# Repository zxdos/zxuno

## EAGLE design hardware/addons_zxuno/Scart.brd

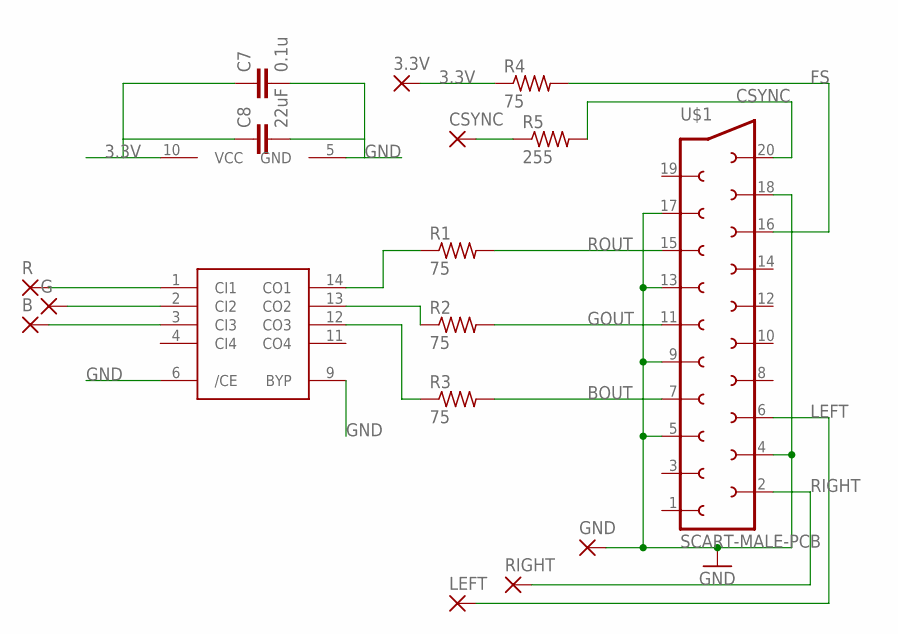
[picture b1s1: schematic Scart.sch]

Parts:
3.3V: WIREPADSMD1,27-254; SMD1,27-2,54
B: WIREPADSMD1,27-254; SMD1,27-2,54
C7: 0.1u; C0805K
C8: 22uF; C0805K
CSYNC: WIREPADSMD1,27-254; SMD1,27-2,54
G: WIREPADSMD1,27-254; SMD1,27-2,54
GND: WIREPADSMD1,27-254; SMD1,27-2,54
LEFT: WIREPADSMD1,27-254; SMD1,27-2,54
R: WIREPADSMD1,27-254; SMD1,27-2,54
R1, R2, R3, R4: 75; R0805
R5: 255; R0805
RIGHT: WIREPADSMD1,27-254; SMD1,27-2,54
U$1: SCART-MALE-PCB; SCART-PCB
U$2: THS7374

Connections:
3.3V: 3.3V.1, C7.1, C8.1, R4.1, U$2.10 (VCC)
BOUT: R3.2, U$1.7
CSYNC: R5.2, U$1.20
FS: R4.2, U$1.16
GND: C7.2, C8.2, GND.1, U$1.4, U$1.5, U$1.9, U$1.13, U$1.17, U$1.18, U$2.5 (GND), U$2.6 (/CE), U$2.9 (BYP)
GOUT: R2.2, U$1.11
LEFT: LEFT.1, U$1.6
unnamed: R.1, U$2.1 (CI1)
unnamed: R1.1, U$2.14 (CO1)
unnamed: R2.1, U$2.13 (CO2)
unnamed: R3.1, U$2.12 (CO3)
unnamed: G.1, U$2.2 (CI2)
unnamed: B.1, U$2.3 (CI3)
unnamed: CSYNC.1, R5.1
RIGHT: RIGHT.1, U$1.2
ROUT: R1.2, U$1.15

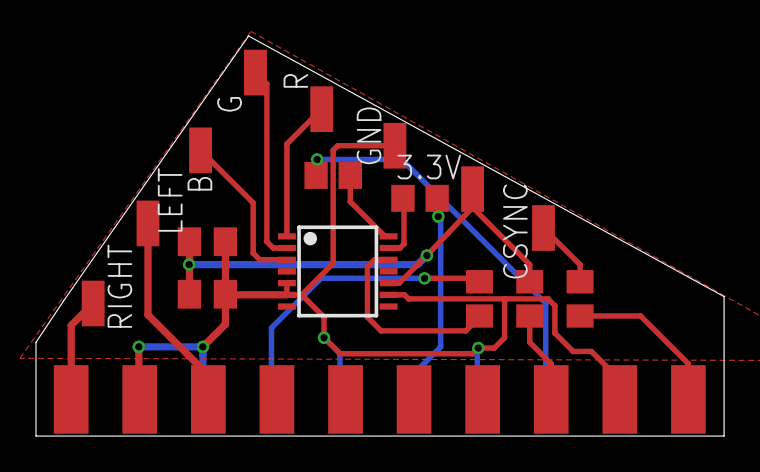
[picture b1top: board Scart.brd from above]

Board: 2 copper layers, 38.2 x 22.2 mm, 17 parts (1 on the bottom side), 16 nets.

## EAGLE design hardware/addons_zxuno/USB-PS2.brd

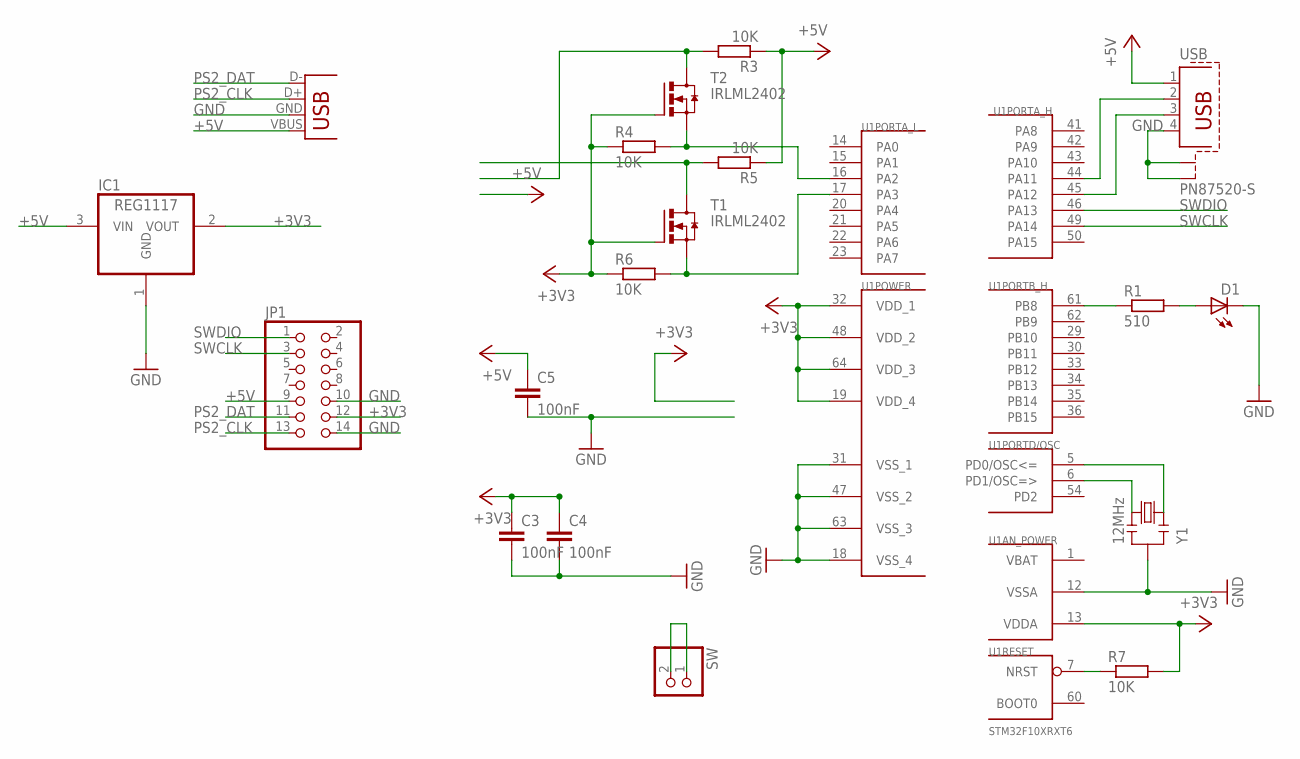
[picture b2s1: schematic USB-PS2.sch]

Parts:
C3, C4, C5: 100nF; C0805
D1: LEDSML0805; SML0805
IC1: REG1117; SOT223
JP1: PINHD-2X7; 2X07
R1: 510; R0805
R3, R4, R5, R6, R7: 10K; R0805
SW: PINHD-1X2; 1X02
T1, T2: IRLML2402; MICRO3
U1: STM32F10XRXT6; TQFP64
USB: PN87520-S
X1: USB-A-H
Y1: 12MHz; RESONATOR

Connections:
+3V3: C3.1, C4.1, IC1.2 (VOUT), JP1.12, R4.1, R6.1, R7.2, T1.1 (G), T2.1 (G), U1.13 (VDDA), U1.19 (VDD_4), U1.32 (VDD_1), U1.48 (VDD_2), U1.64 (VDD_3)
+5V: C5.1, IC1.3 (VIN), JP1.9, R3.1, R5.1, USB.1, X1.VBUS (GND)
GND: C3.2, C4.2, C5.2, D1.C, IC1.1 (GND), JP1.10, JP1.14, U1.12 (VSSA), U1.18 (VSS_4), U1.31 (VSS_1), U1.47 (VSS_2), U1.63 (VSS_3), USB.4, USB.S1, USB.S2, X1.GND (VBUS), Y1.2
unnamed: U1.44 (PA11), USB.2
unnamed: U1.45 (PA12), USB.3
unnamed: R1.1, U1.61 (PB8)
unnamed: U1.5 (PD0/OSC<=), Y1.1
unnamed: D1.A, R1.2
unnamed: U1.6 (PD1/OSC=>), Y1.3
unnamed: R7.1, U1.7 (NRST)
unnamed: SW.1, SW.2
unnamed: R6.2, T1.2 (S), U1.17 (PA3)
unnamed: R4.2, T2.2 (S), U1.16 (PA2)
PS2_CLK: JP1.13, R5.2, T1.3 (D), X1.D+ (D-)
PS2_DAT: JP1.11, R3.2, T2.3 (D), X1.D- (D+)
SWCLK: JP1.3, U1.49 (PA14)
SWDIO: JP1.1, U1.46 (PA13)
VBAT: U1.1 (VBAT)

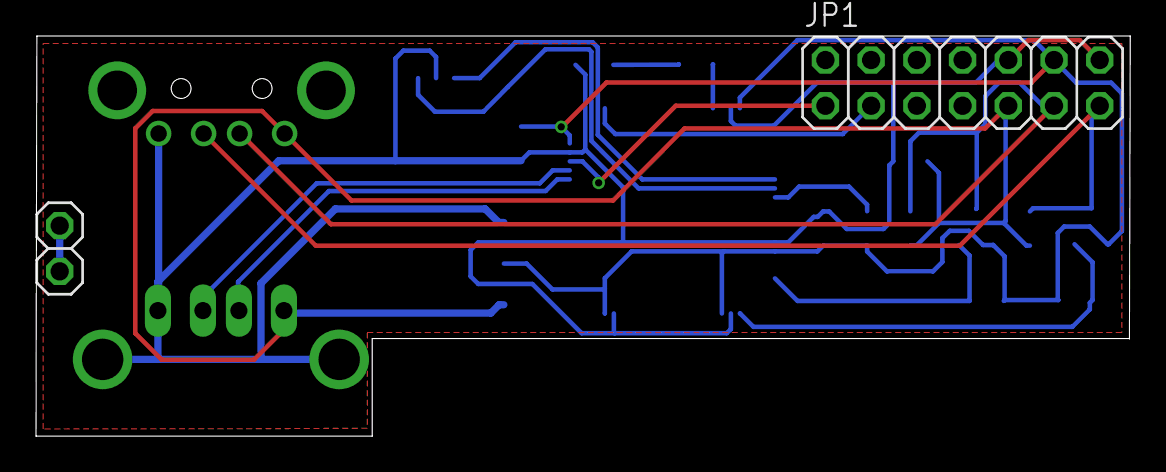
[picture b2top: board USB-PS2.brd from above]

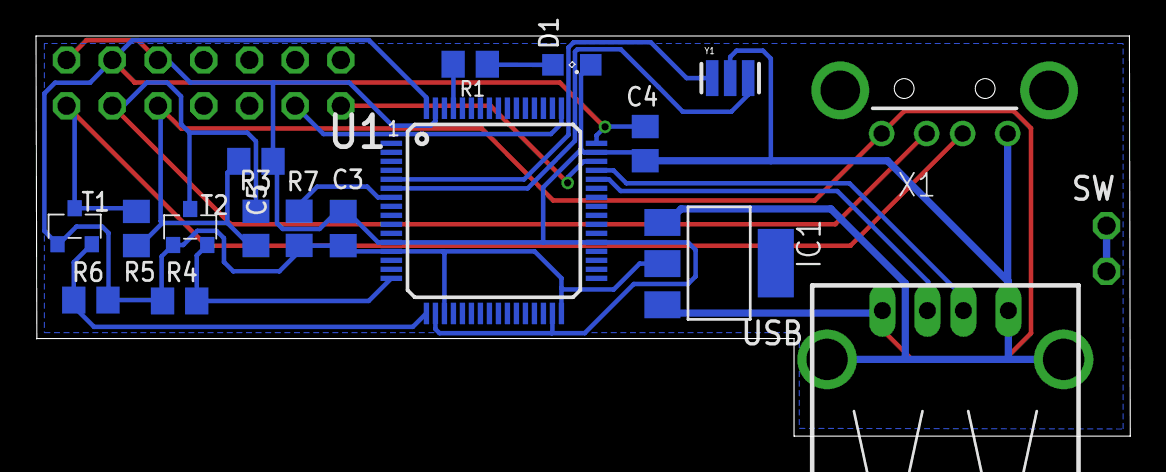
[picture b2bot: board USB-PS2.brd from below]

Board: 2 copper layers, 60.8 x 22.2 mm, 19 parts (17 on the bottom side), 17 nets.

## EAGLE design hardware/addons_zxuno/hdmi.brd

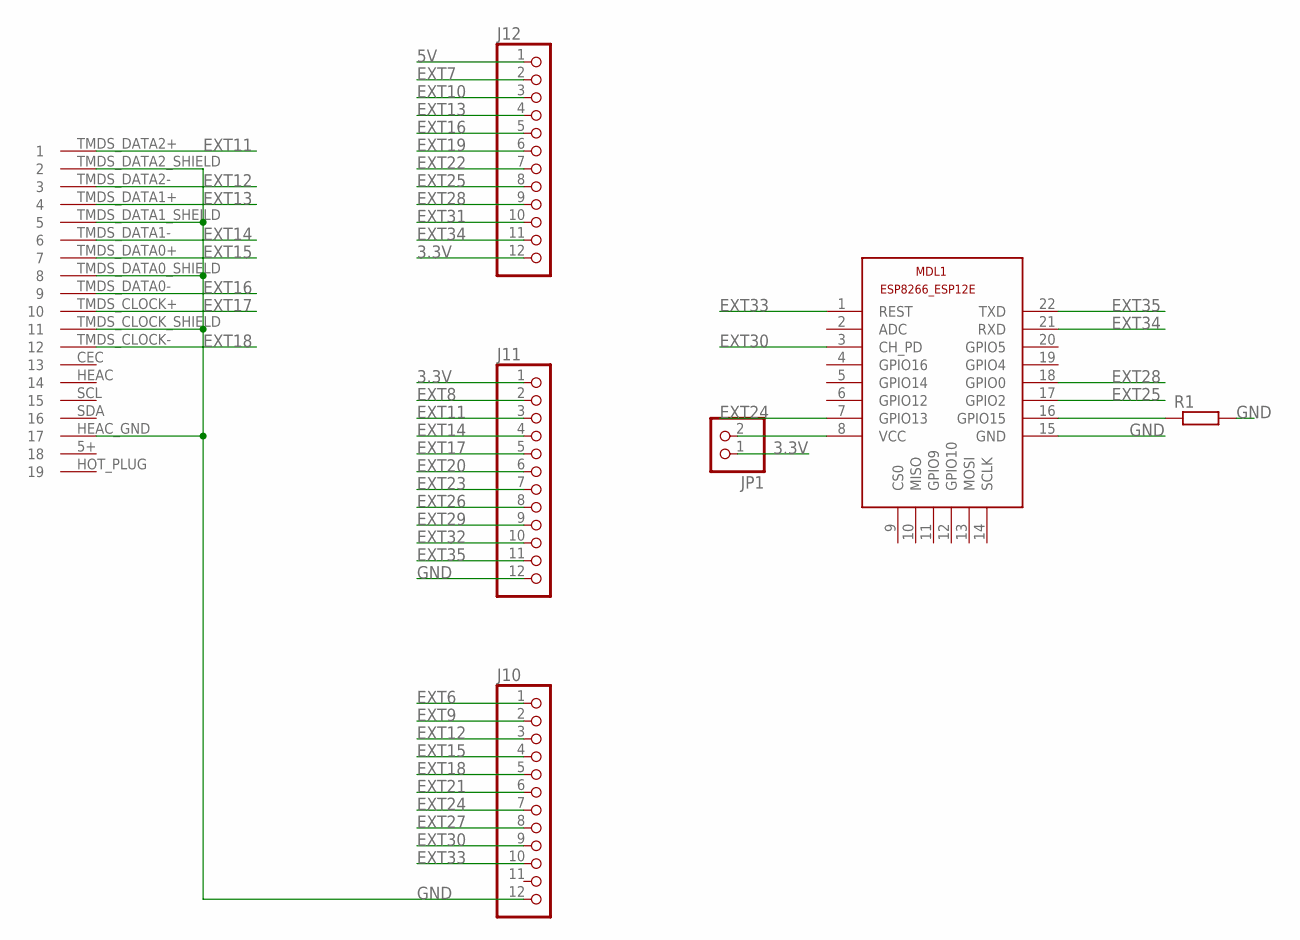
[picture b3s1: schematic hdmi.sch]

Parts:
J10, J11, J12: PINHD-1X12; 1X12
JP1: PINHD-1X2/90; 1X02/90
MDL1: ESP8266-12EESP8266-ESP12E; ESP8266-ESP12E
R1: R-EU_M0805; M0805
U$2: HDMI; DS1115

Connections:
3.3V: J11.1, J12.12, JP1.1
5V: J12.1
EXT6: J10.1
EXT7: J12.2
EXT8: J11.2
EXT9: J10.2
EXT10: J12.3
EXT11: J11.3, U$2.TMDS_DATA2+ (1)
EXT12: J10.3, U$2.TMDS_DATA2- (3)
EXT13: J12.4, U$2.TMDS_DATA1+ (4)
EXT14: J11.4, U$2.TMDS_DATA1- (6)
EXT15: J10.4, U$2.TMDS_DATA0+ (7)
EXT16: J12.5, U$2.TMDS_DATA0- (9)
EXT17: J11.5, U$2.TMDS_CLOCK+ (10)
EXT18: J10.5, U$2.TMDS_CLOCK- (12)
EXT19: J12.6
EXT20: J11.6
EXT21: J10.6
EXT22: J12.7
EXT23: J11.7
EXT24: J10.7, MDL1.7 (GPIO13)
EXT25: J12.8, MDL1.17 (GPIO2)
EXT26: J11.8
EXT27: J10.8
EXT28: J12.9, MDL1.18 (GPIO0)
EXT29: J11.9
EXT30: J10.9, MDL1.3 (CH_PD)
EXT31: J12.10
EXT32: J11.10
EXT33: J10.10, MDL1.1 (REST)
EXT34: J12.11, MDL1.21 (RXD)
EXT35: J11.11, MDL1.22 (TXD)
GND: J10.12, J11.12, MDL1.15 (GND), R1.2, U$2.HEAC_GND (17), U$2.TMDS_CLOCK_SHIELD (11), U$2.TMDS_DATA0_SHIELD (8), U$2.TMDS_DATA1_SHEILD (5), U$2.TMDS_DATA2_SHIELD (2)
unnamed: MDL1.16 (GPIO15), R1.1
unnamed: JP1.2, MDL1.8 (VCC)

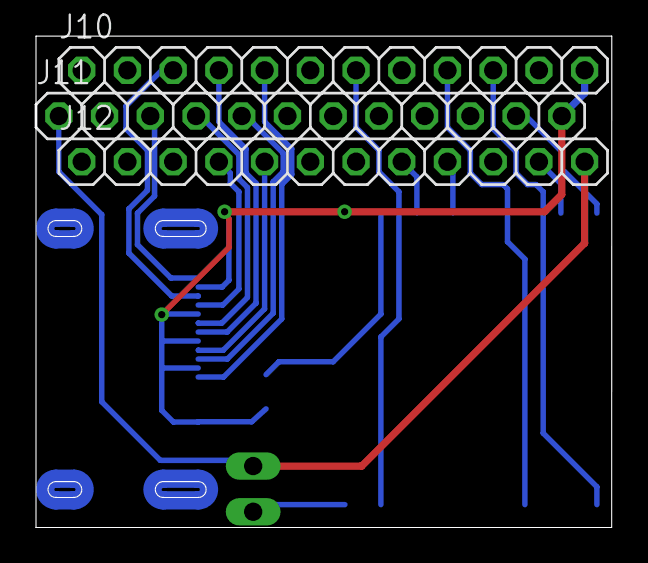
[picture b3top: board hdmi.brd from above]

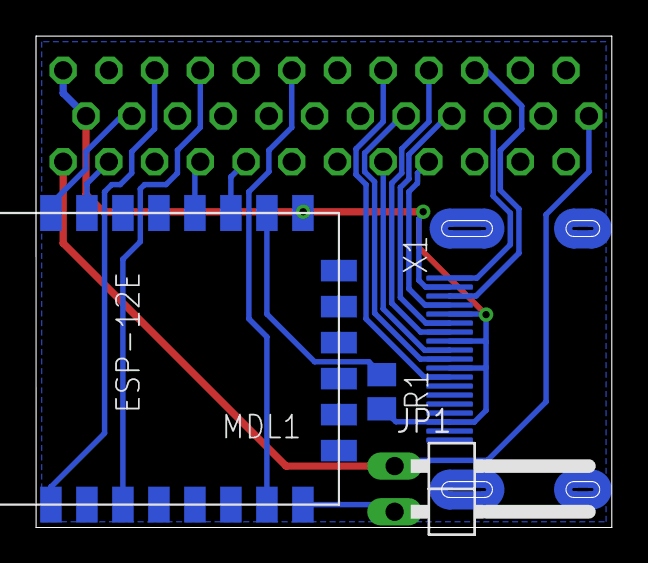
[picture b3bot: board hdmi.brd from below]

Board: 2 copper layers, 32.0 x 27.3 mm, 7 parts (4 on the bottom side), 19 nets.

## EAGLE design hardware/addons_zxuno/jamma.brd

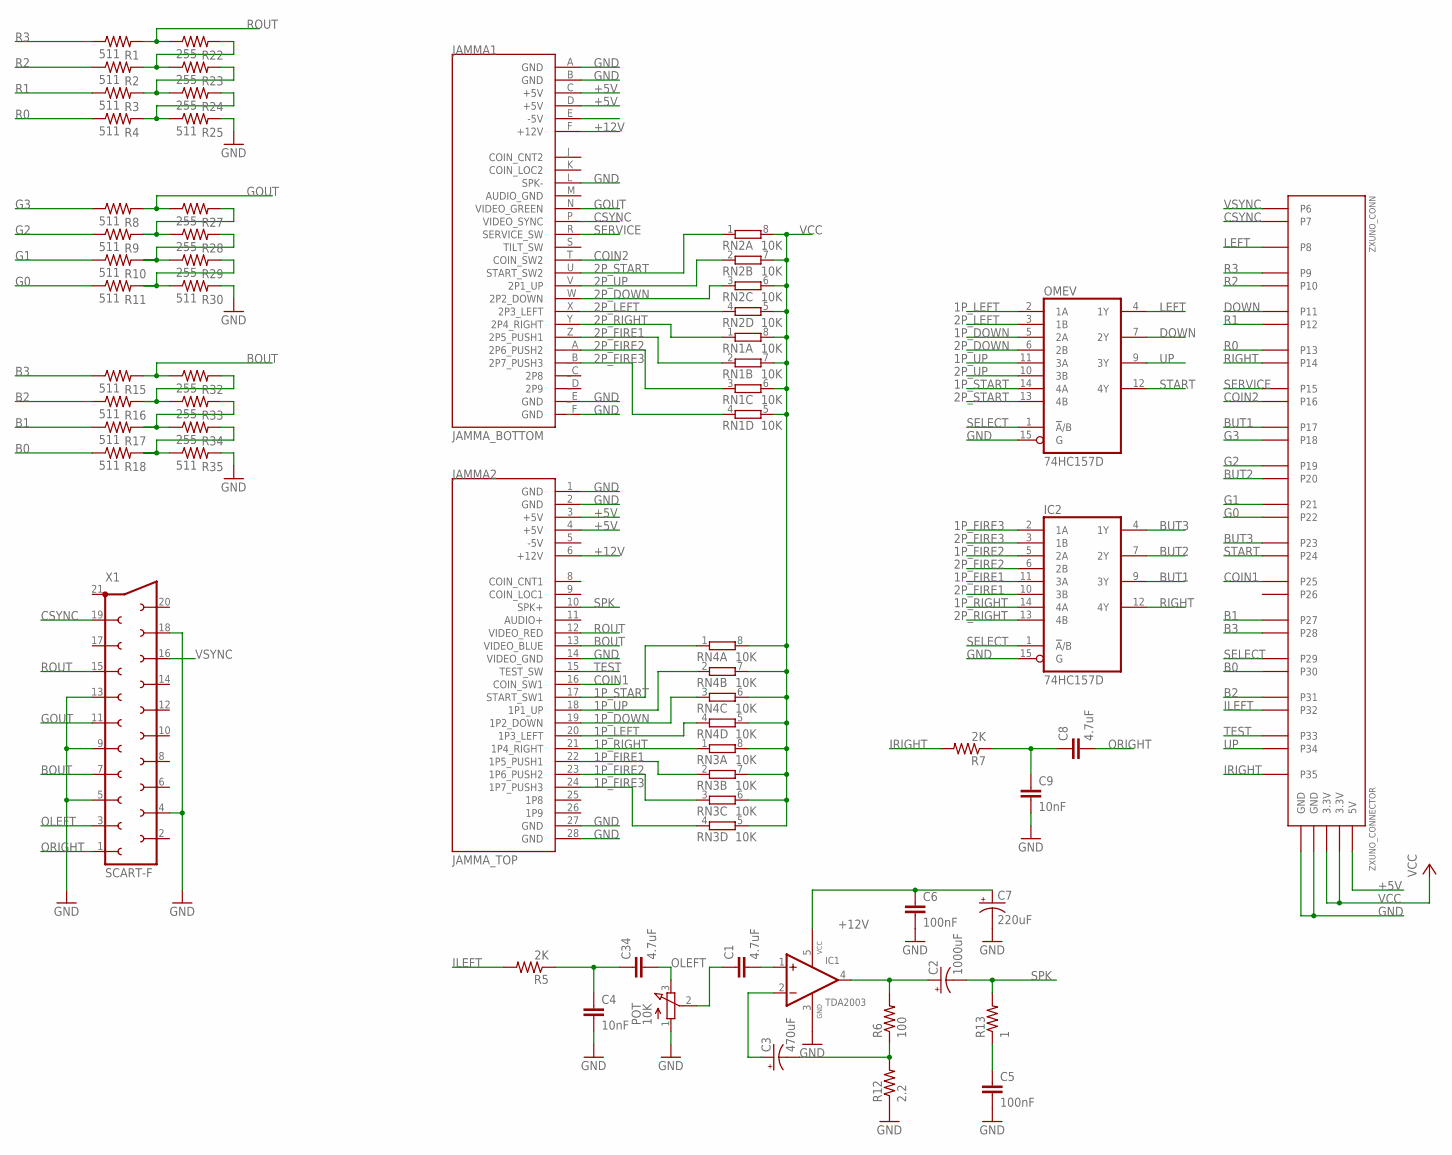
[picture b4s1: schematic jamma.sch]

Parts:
C1, C8, C34: 4.7uF; C0805
C2: 1000uF; E5-13
C3: 470uF; E5-10,5
C4, C9: 10nF; C0805
C5, C6: 100nF; C0805K
C7: 220uF; E5-10,5
IC1: TDA2003; PENTAWATT-V
IC2: 74HC157D; SO16
JAMMA1: JAMMA_BOTTOM
JAMMA2: JAMMA_TOP
OMEV: 74HC157D; SO16
POT: 10K; POT
R1, R2, R3, R4, R8, R9, R10, R11, R15, R16, R17, R18, R25, R30, R35: 511; R0805
R5, R7: 2K; M0805
R6: 100; R0805
R12: 2.2; R0805
R13: 1; R0805
R22, R23, R24, R27, R28, R29, R32, R33, R34: 255; R0805
RN1, RN2, RN3, RN4: 10K; 0603-ARC
X1: SCART-F
ZXUNO_CONN: ZXUNO_CONNECTOR

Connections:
1P_DOWN: JAMMA2.19 (1P2_DOWN), OMEV.5 (2A), RN4.3 (1)
1P_FIRE1: IC2.11 (3A), JAMMA2.22 (1P5_PUSH1), RN3.2 (1)
1P_FIRE2: IC2.5 (2A), JAMMA2.23 (1P6_PUSH2), RN3.3 (1)
1P_FIRE3: IC2.2 (1A), JAMMA2.24 (1P7_PUSH3), RN3.4 (1)
1P_LEFT: JAMMA2.20 (1P3_LEFT), OMEV.2 (1A), RN4.4 (1)
1P_RIGHT: IC2.14 (4A), JAMMA2.21 (1P4_RIGHT), RN3.1
1P_START: JAMMA2.17 (START_SW1), OMEV.14 (4A), RN4.1
1P_UP: JAMMA2.18 (1P1_UP), OMEV.11 (3A), RN4.2 (1)
2P_DOWN: JAMMA1.W (2P2_DOWN), OMEV.6 (2B), RN2.3 (1)
2P_FIRE1: IC2.10 (3B), JAMMA1.Z (2P5_PUSH1), RN1.2 (1)
2P_FIRE2: IC2.6 (2B), JAMMA1._A (2P6_PUSH2), RN1.3 (1)
2P_FIRE3: IC2.3 (1B), JAMMA1._B (2P7_PUSH3), RN1.4 (1)
2P_LEFT: JAMMA1.X (2P3_LEFT), OMEV.3 (1B), RN2.4 (1)
2P_RIGHT: IC2.13 (4B), JAMMA1.Y (2P4_RIGHT), RN1.1
2P_START: JAMMA1.U (START_SW2), OMEV.13 (4B), RN2.1
2P_UP: JAMMA1.V (2P1_UP), OMEV.10 (3B), RN2.2 (1)
+5V: JAMMA1.C (+5V), JAMMA1.D (+5V), JAMMA2.3 (+5V), JAMMA2.4 (+5V), ZXUNO_CONN.5V
+12V: C6.1, C7.+, IC1.5 (VCC), JAMMA1.F (+12V), JAMMA2.6 (+12V)
-5V: JAMMA2.5 (-5V)
B0: R18.1, ZXUNO_CONN.P30
B1: R17.1, ZXUNO_CONN.P27
B2: R16.1, ZXUNO_CONN.P31
B3: R15.1, ZXUNO_CONN.P28
BOUT: JAMMA2.13 (VIDEO_BLUE), R15.2, R32.1, X1.7
BUT1: IC2.9 (3Y), ZXUNO_CONN.P17
BUT2: IC2.7 (2Y), ZXUNO_CONN.P20
BUT3: IC2.4 (1Y), ZXUNO_CONN.P23
COIN1: JAMMA2.16 (COIN_SW1), ZXUNO_CONN.P25
COIN2: JAMMA1.T (COIN_SW2), ZXUNO_CONN.P16
CSYNC: JAMMA1.P (VIDEO_SYNC), X1.19, ZXUNO_CONN.P7
DOWN: OMEV.7 (2Y), ZXUNO_CONN.P11
G0: R11.1, ZXUNO_CONN.P22
G1: R10.1, ZXUNO_CONN.P21
G2: R9.1, ZXUNO_CONN.P19
G3: R8.1, ZXUNO_CONN.P18
GND: C4.2, C5.2, C6.2, C7.-, C9.2, IC1.3 (GND), IC2.8 (GND), IC2.15 (G), JAMMA1.A (GND), JAMMA1.B (GND), JAMMA1.L (SPK-), JAMMA1._E (GND), JAMMA1._F (GND), JAMMA2.1 (GND), JAMMA2.2 (GND), JAMMA2.14 (VIDEO_GND), JAMMA2.27 (GND), JAMMA2.28 (GND), OMEV.8 (GND), OMEV.15 (G), POT.1 (A), R12.1, R25.2, R30.2, R35.2, X1.4, X1.5, X1.9, X1.13, X1.18, ZXUNO_CONN.GND@1 (GND), ZXUNO_CONN.GND@2 (GND)
GOUT: JAMMA1.N (VIDEO_GREEN), R8.2, R27.1, X1.11
ILEFT: R5.2, ZXUNO_CONN.P32
IRIGHT: R7.2, ZXUNO_CONN.P35
LEFT: OMEV.4 (1Y), ZXUNO_CONN.P8
unnamed: C8.1, C9.1, R7.1
unnamed: C1.2, IC1.1 (+IN)
unnamed: C1.1, POT.2 (S)
unnamed: C3.+, IC1.2 (-IN)
unnamed: C3.-, R6.1, R12.2
unnamed: R9.2, R27.2, R28.1
unnamed: C2.+, IC1.4 (OUT), R6.2
unnamed: C4.1, C34.1, R5.1
unnamed: C5.1, R13.1
unnamed: R2.2, R22.2, R23.1
unnamed: R3.2, R23.2, R24.1
unnamed: R4.2, R24.2, R25.1
unnamed: R11.2, R29.2, R30.1
unnamed: R10.2, R28.2, R29.1
unnamed: R16.2, R32.2, R33.1
unnamed: R17.2, R33.2, R34.1
unnamed: R18.2, R34.2, R35.1
OLEFT: C34.2, POT.3 (E), X1.3
ORIGHT: C8.2, X1.1
R0: R4.1, ZXUNO_CONN.P13
R1: R3.1, ZXUNO_CONN.P12
R2: R2.1, ZXUNO_CONN.P10
R3: R1.1, ZXUNO_CONN.P9
RIGHT: IC2.12 (4Y), ZXUNO_CONN.P14
ROUT: JAMMA2.12 (VIDEO_RED), R1.2, R22.1, X1.15
SELECT: IC2.1 (!A!/B), OMEV.1 (!A!/B), ZXUNO_CONN.P29
SERVICE: JAMMA1.R (SERVICE_SW), ZXUNO_CONN.P15
SPK: C2.-, JAMMA2.10 (SPK+), R13.2
START: OMEV.12 (4Y), ZXUNO_CONN.P24
TEST: JAMMA2.15 (TEST_SW), ZXUNO_CONN.P33
UP: OMEV.9 (3Y), ZXUNO_CONN.P34
VCC: IC2.16 (VCC), OMEV.16 (VCC), RN1.5 (2), RN1.6 (2), RN1.7 (2), RN1.8 (2), RN2.5 (2), RN2.6 (2), RN2.7 (2), RN2.8 (2), RN3.5 (2), RN3.6 (2), RN3.7 (2), RN3.8 (2), RN4.5 (2), RN4.6 (2), RN4.7 (2), RN4.8 (2), ZXUNO_CONN.3.3V@1 (3.3V), ZXUNO_CONN.3.3V@2 (3.3V)
VSYNC: X1.16, ZXUNO_CONN.P6

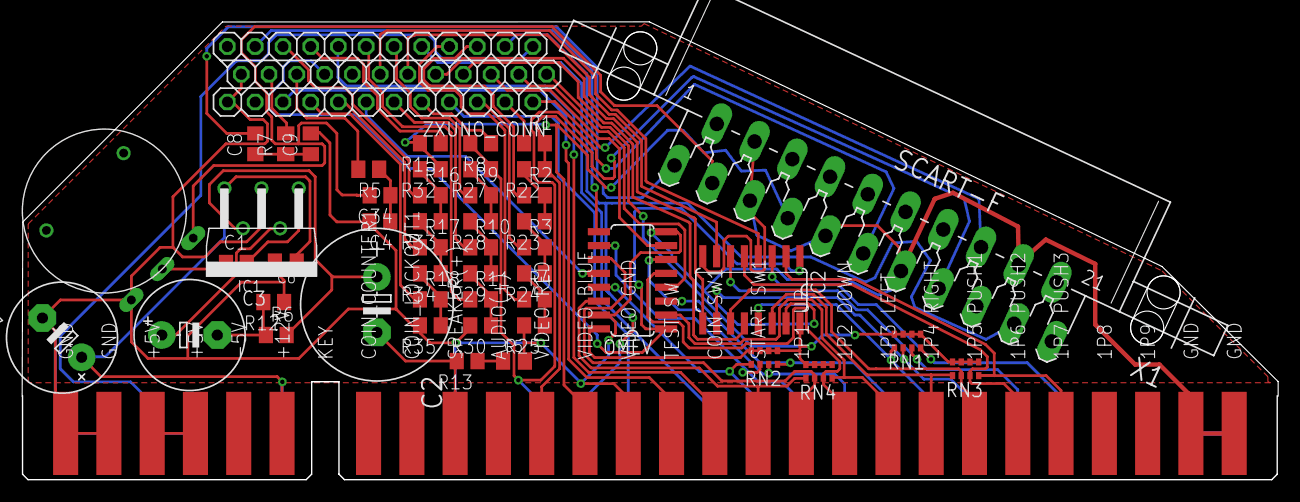
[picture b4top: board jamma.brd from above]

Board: 2 copper layers, 114.9 x 41.9 mm, 51 parts (0 on the bottom side), 72 nets.

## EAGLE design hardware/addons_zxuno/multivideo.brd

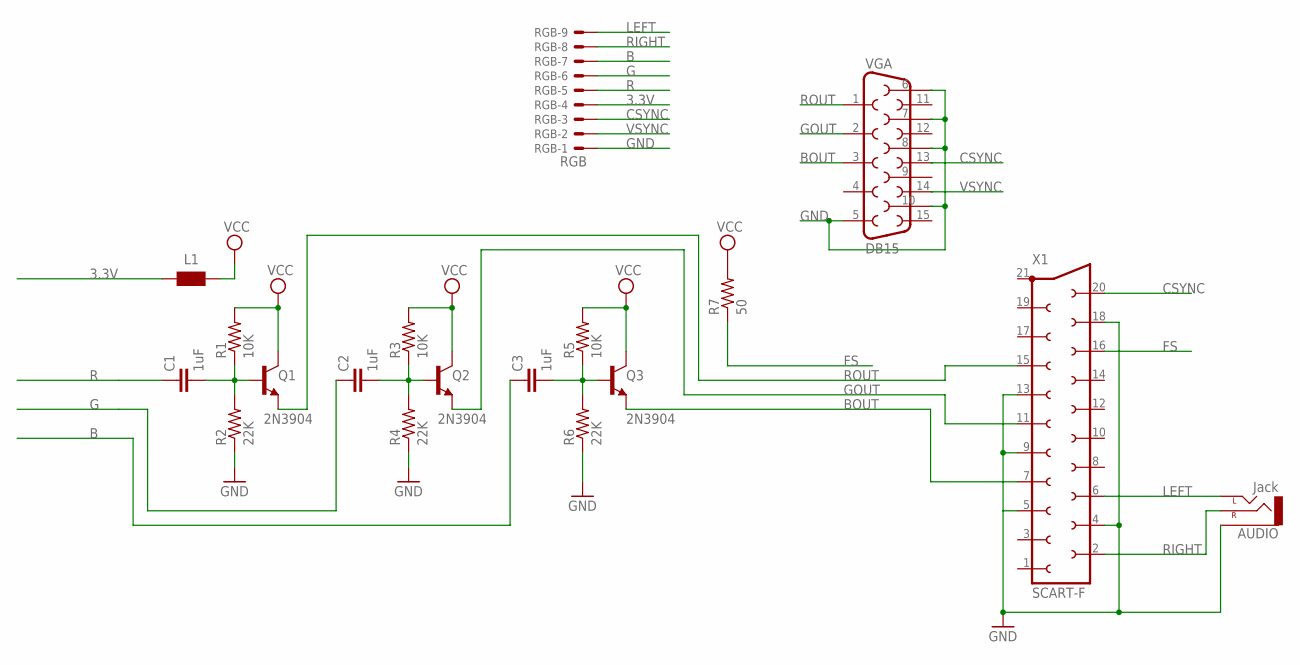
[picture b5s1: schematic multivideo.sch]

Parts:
AUDIO: Jack; AUDIO-JACK
C1, C2, C3: 1uF; C1206K
L1: WE-CBF_0805; 0805
Q1, Q2, Q3: 2N3904; SOT23
R1, R3, R5: 10K; R0805
R2, R4, R6: 22K; R0805
R7: 50; R0805
RGB: RGB; 53048-09
VGA: DB15
X1: SCART-F

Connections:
3.3V: L1.1, RGB.4
B: C3.1, RGB.7
BOUT: Q3.2 (E), VGA.3, X1.7
CSYNC: RGB.3, VGA.13, X1.20
FS: R7.1, X1.16
G: C2.1, RGB.6
GND: AUDIO.SLEEVE, R2.1, R4.1, R6.1, RGB.1, VGA.5, VGA.6, VGA.7, VGA.8, VGA.10, X1.4, X1.5, X1.9, X1.13, X1.18
GOUT: Q2.2 (E), VGA.2, X1.11
LEFT: AUDIO.TIP (LEFT), RGB.9, X1.6
unnamed: C1.2, Q1.1 (B), R1.1, R2.2
unnamed: C3.2, Q3.1 (B), R5.1, R6.2
unnamed: C2.2, Q2.1 (B), R3.1, R4.2
R: C1.1, RGB.5
RIGHT: AUDIO.RING (RIGHT), RGB.8, X1.2
ROUT: Q1.2 (E), VGA.1, X1.15
VCC: L1.2, Q1.3 (C), Q2.3 (C), Q3.3 (C), R1.2, R3.2, R5.2, R7.2
VSYNC: RGB.2, VGA.14

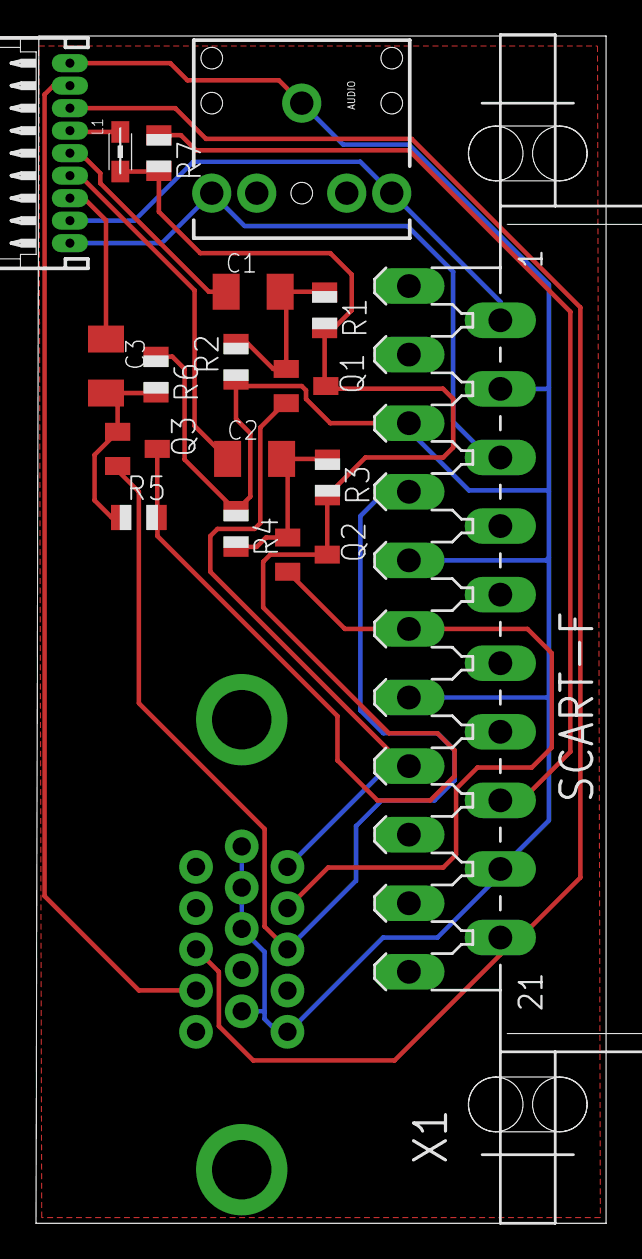
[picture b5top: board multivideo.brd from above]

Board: 2 copper layers, 31.7 x 66.0 mm, 18 parts (1 on the bottom side), 17 nets.

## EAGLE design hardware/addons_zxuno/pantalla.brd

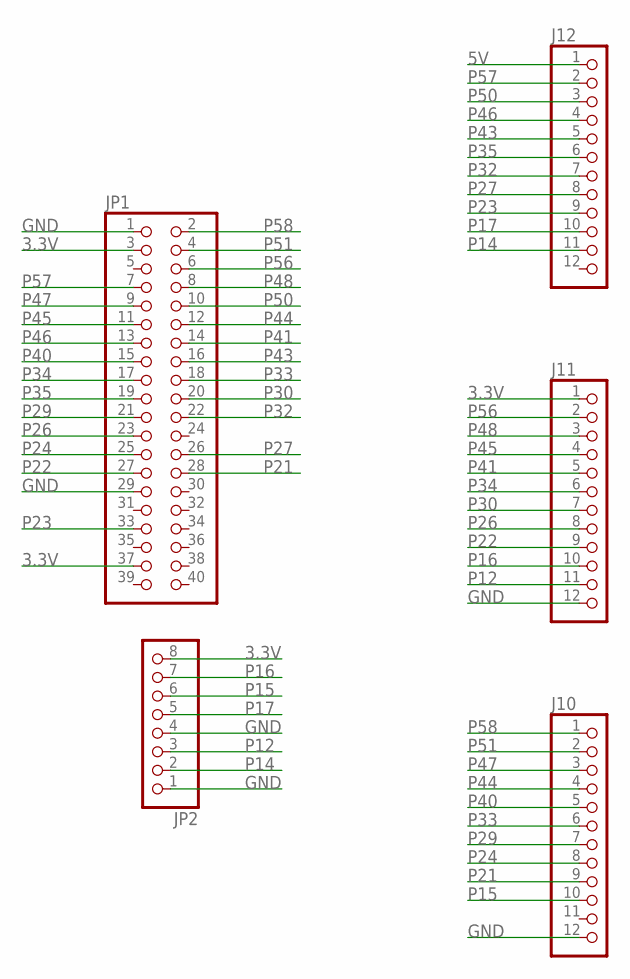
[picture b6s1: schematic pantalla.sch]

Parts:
J10, J11, J12: PINHD-1X12; 1X12
JP1: PINHD-2X20; 2X20
JP2: PINHD-1X8; 1X08

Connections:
3.3V: J11.1, JP1.3, JP1.37, JP2.8
5V: J12.1
GND: J10.12, J11.12, JP1.1, JP1.29, JP2.1, JP2.4
P12: J11.11, JP2.3
P14: J12.11, JP2.2
P15: J10.10, JP2.6
P16: J11.10, JP2.7
P17: J12.10, JP2.5
P21: J10.9, JP1.28
P22: J11.9, JP1.27
P23: J12.9, JP1.33
P24: J10.8, JP1.25
P26: J11.8, JP1.23
P27: J12.8, JP1.26
P29: J10.7, JP1.21
P30: J11.7, JP1.20
P32: J12.7, JP1.22
P33: J10.6, JP1.18
P34: J11.6, JP1.17
P35: J12.6, JP1.19
P40: J10.5, JP1.15
P41: J11.5, JP1.14
P43: J12.5, JP1.16
P44: J10.4, JP1.12
P45: J11.4, JP1.11
P46: J12.4, JP1.13
P47: J10.3, JP1.9
P48: J11.3, JP1.8
P50: J12.3, JP1.10
P51: J10.2, JP1.4
P56: J11.2, JP1.6
P57: J12.2, JP1.7
P58: J10.1, JP1.2

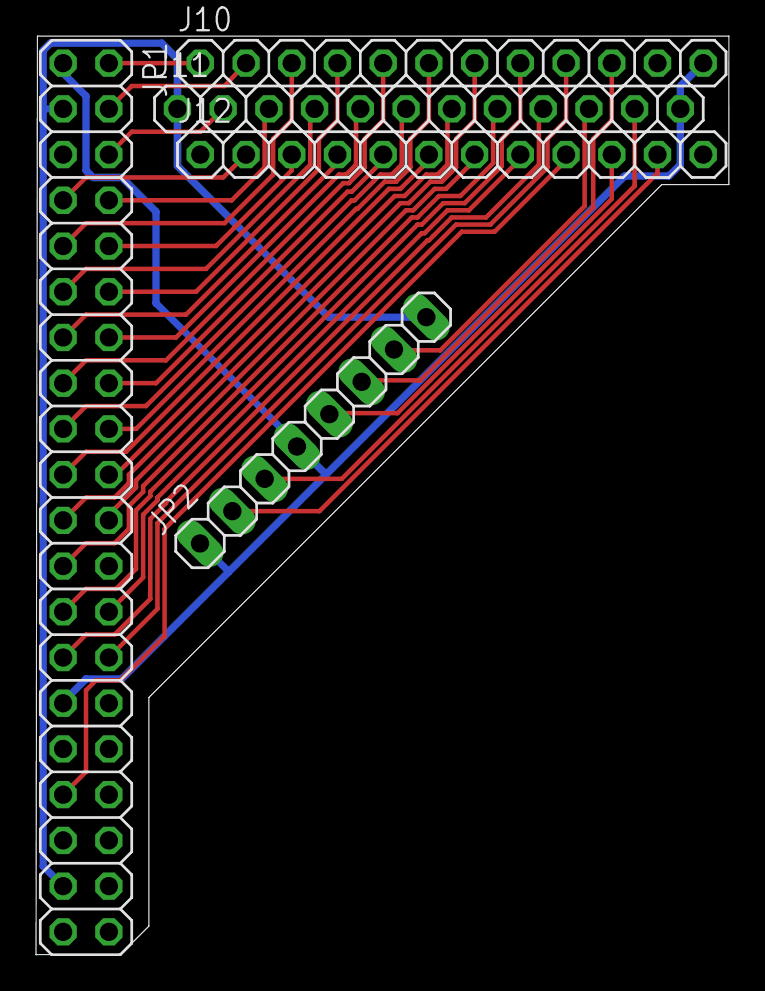
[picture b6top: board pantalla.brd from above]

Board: 2 copper layers, 38.5 x 51.0 mm, 5 parts (0 on the bottom side), 32 nets.

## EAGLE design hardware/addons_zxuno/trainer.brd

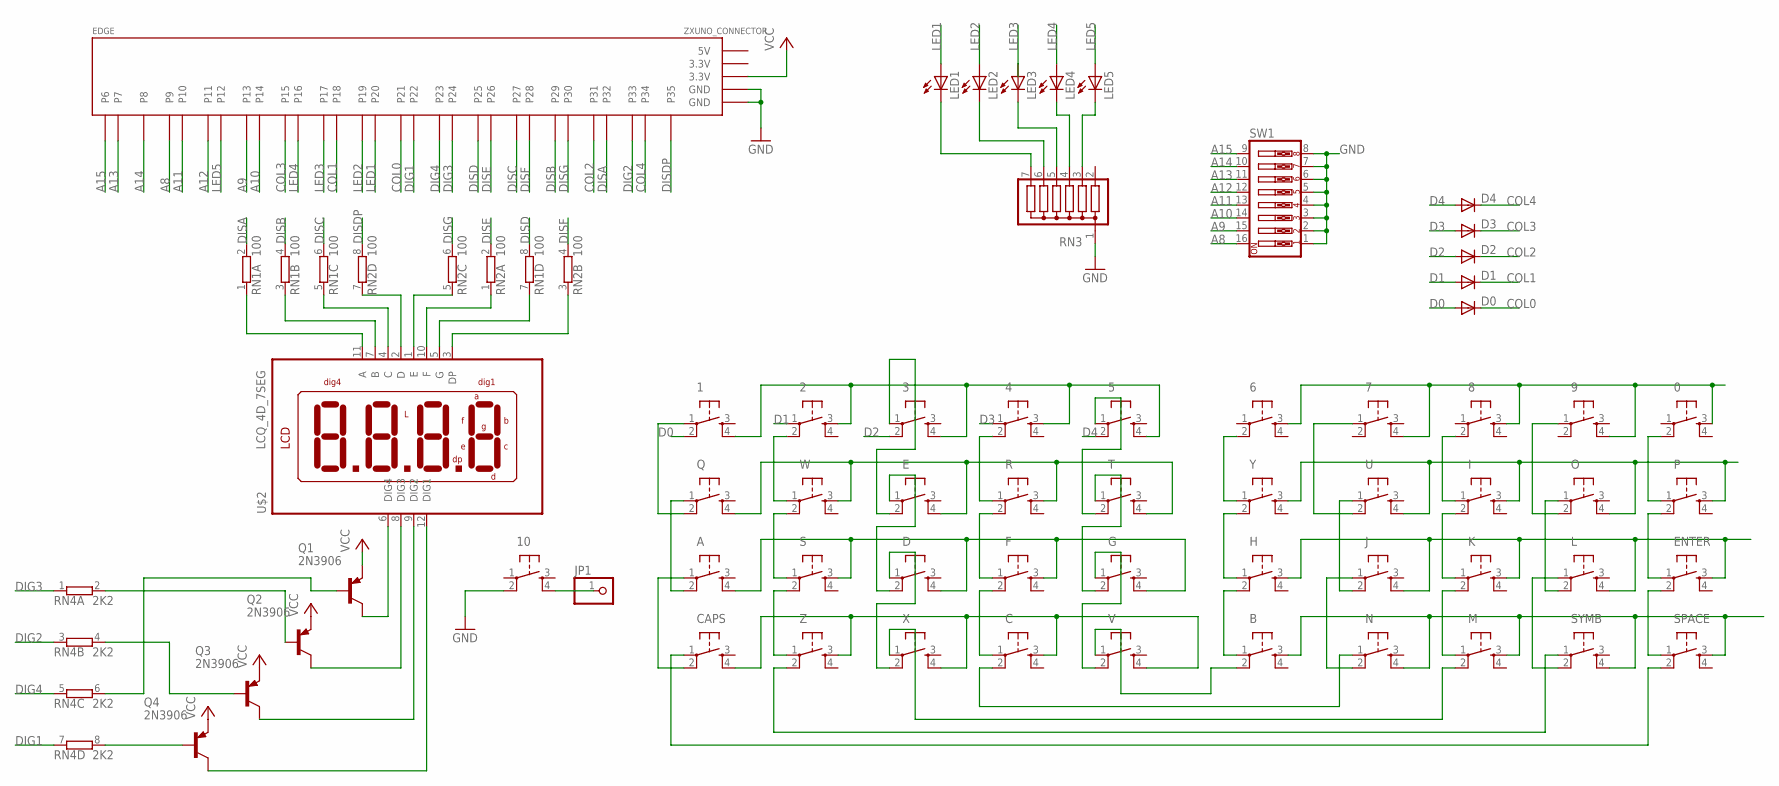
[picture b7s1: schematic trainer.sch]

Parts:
0, 1, 2, 3, 4, 5, 6, 7, 8, 9, 10: DTS-6
A: DTS-6
B: DTS-6
C: DTS-6
CAPS: DTS-6
D: DTS-6
D0, D1, D2, D3, D4: 1N4148DO35-7; DO35-7
E: DTS-6
EDGE: ZXUNO_CONNECTOR
ENTER: DTS-6
F: DTS-6
G: DTS-6
H: DTS-6
I: DTS-6
J: DTS-6
JP1: PINHD-1X1; 1X01
K: DTS-6
L: DTS-6
LED1, LED2, LED3, LED4, LED5: LED3MM
M: DTS-6
N: DTS-6
O: DTS-6
P: DTS-6
Q: DTS-6
Q1, Q2, Q3, Q4: 2N3906; TO92
R: DTS-6
RN1, RN2: 100; SIL8
RN3: G06R; SIL7
RN4: 2K2; SIL8
S: DTS-6
SPACE: DTS-6
SW1: SW_DIP-8; EDG-08
SYMB: DTS-6
T: DTS-6
U: DTS-6
U$2: LCQ_4D_7SEG; LDQ_4D_7SEG
V: DTS-6
W: DTS-6
X: DTS-6
Y: DTS-6
Z: DTS-6

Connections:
3.3V: EDGE.3.3V@1 (3.3V)
5V: EDGE.5V
A8: C.3, CAPS.4, EDGE.P9, SW1.16, V.4, X.4, Z.3
A9: A.4, D.4, EDGE.P13, F.3, G.4, S.3, SW1.15
A10: E.4, EDGE.P14, Q.4, R.3, SW1.14, T.4, W.3
A11: 1.4, 2.3, 3.4, 4.3, 5.4, EDGE.P10, SW1.13
A12: 0.3, 6.3, 7.4, 8.3, 9.4, EDGE.P11, SW1.12
A13: EDGE.P7, I.3, O.4, P.3, SW1.11, U.4, Y.3
A14: EDGE.P8, ENTER.3, H.3, J.4, K.3, L.4, SW1.10
A15: B.3, EDGE.P6, M.3, N.4, SPACE.3, SW1.9, SYMB.4
COL0: D0.C, EDGE.P21
COL1: D1.C, EDGE.P18
COL2: D2.C, EDGE.P31
COL3: D3.C, EDGE.P15
COL4: D4.C, EDGE.P34
D0: 1.2, D0.A
D1: 2.1, D1.A
D2: 3.2, D2.A
D3: 4.1, D3.A
D4: 5.2, D4.A
DIG1: EDGE.P22, RN4.7 (1)
DIG2: EDGE.P33, RN4.3 (1)
DIG3: EDGE.P24, RN4.1
DIG4: EDGE.P23, RN4.5 (1)
DISA: EDGE.P32, RN1.2
DISB: EDGE.P29, RN1.4 (2)
DISC: EDGE.P27, RN1.6 (2)
DISD: EDGE.P25, RN1.8 (2)
DISDP: EDGE.P35, RN2.8 (2)
DISE: EDGE.P26, RN2.2
DISF: EDGE.P28, RN2.4 (2)
DISG: EDGE.P30, RN2.6 (2)
ELETE: M.2, X.1
GND: 10.2, EDGE.GND@1 (GND), EDGE.GND@2 (GND), RN3.1, SW1.1, SW1.2, SW1.3, SW1.4, SW1.5, SW1.6, SW1.7, SW1.8
LED1: EDGE.P20, LED1.A
LED2: EDGE.P19, LED2.A
LED3: EDGE.P17, LED3.A
LED4: EDGE.P16, LED4.A
LED5: EDGE.P12, LED5.A
unnamed: Q1.1 (C), U$2.6 (DIG4)
unnamed: Q2.1 (C), U$2.8 (DIG3)
unnamed: Q3.1 (C), U$2.9 (DIG2)
unnamed: Q4.1 (C), U$2.12 (DIG1)
unnamed: Q2.2 (B), RN4.2
unnamed: Q1.2 (B), RN4.6 (2)
unnamed: Q3.2 (B), RN4.4 (2)
unnamed: Q4.2 (B), RN4.8 (2)
unnamed: RN1.1, U$2.11 (A)
unnamed: RN1.3 (1), U$2.7 (B)
unnamed: RN1.5 (1), U$2.4 (C)
unnamed: RN2.7 (1), U$2.2 (D)
unnamed: RN2.5 (1), U$2.1 (E)
unnamed: RN2.1, U$2.10 (F)
unnamed: 10.4, JP1.1
unnamed: S.1, W.2
unnamed: S.2, Z.1
unnamed: RN2.3 (1), U$2.3 (DP)
unnamed: SYMB.1, Z.2
unnamed: RN1.7 (1), U$2.5 (G)
unnamed: C.1, F.2
unnamed: CAPS.1, SPACE.2
unnamed: 4.2, R.1
unnamed: F.1, R.2
unnamed: LED4.K (C), RN3.4
unnamed: LED5.K (C), RN3.3
unnamed: LED3.K (C), RN3.5
unnamed: B.2, V.1
unnamed: 5.1, T.2
unnamed: G.2, T.1
unnamed: A.2, Q.1
unnamed: J.2, U.1
unnamed: J.1, N.2
unnamed: 3.1, E.2
unnamed: D.2, E.1
unnamed: A.1, CAPS.2
unnamed: 1.1, Q.2
unnamed: K.2, M.1
unnamed: 2.2, W.1
unnamed: 7.1, U.2
unnamed: LED2.K (C), RN3.6
unnamed: G.1, V.2
unnamed: C.2, N.1
unnamed: L.1, SYMB.2
unnamed: LED1.K (C), RN3.7
unnamed: I.2, K.1
unnamed: 8.2, I.1
unnamed: L.2, O.1
unnamed: B.1, H.2
unnamed: H.1, Y.2
unnamed: ENTER.2, SPACE.1
unnamed: ENTER.1, P.2
unnamed: 0.2, P.1
unnamed: 6.2, Y.1
unnamed: 9.1, O.2
unnamed: D.1, X.2
VCC: EDGE.3.3V@2 (3.3V), Q1.3 (E), Q2.3 (E), Q3.3 (E), Q4.3 (E)

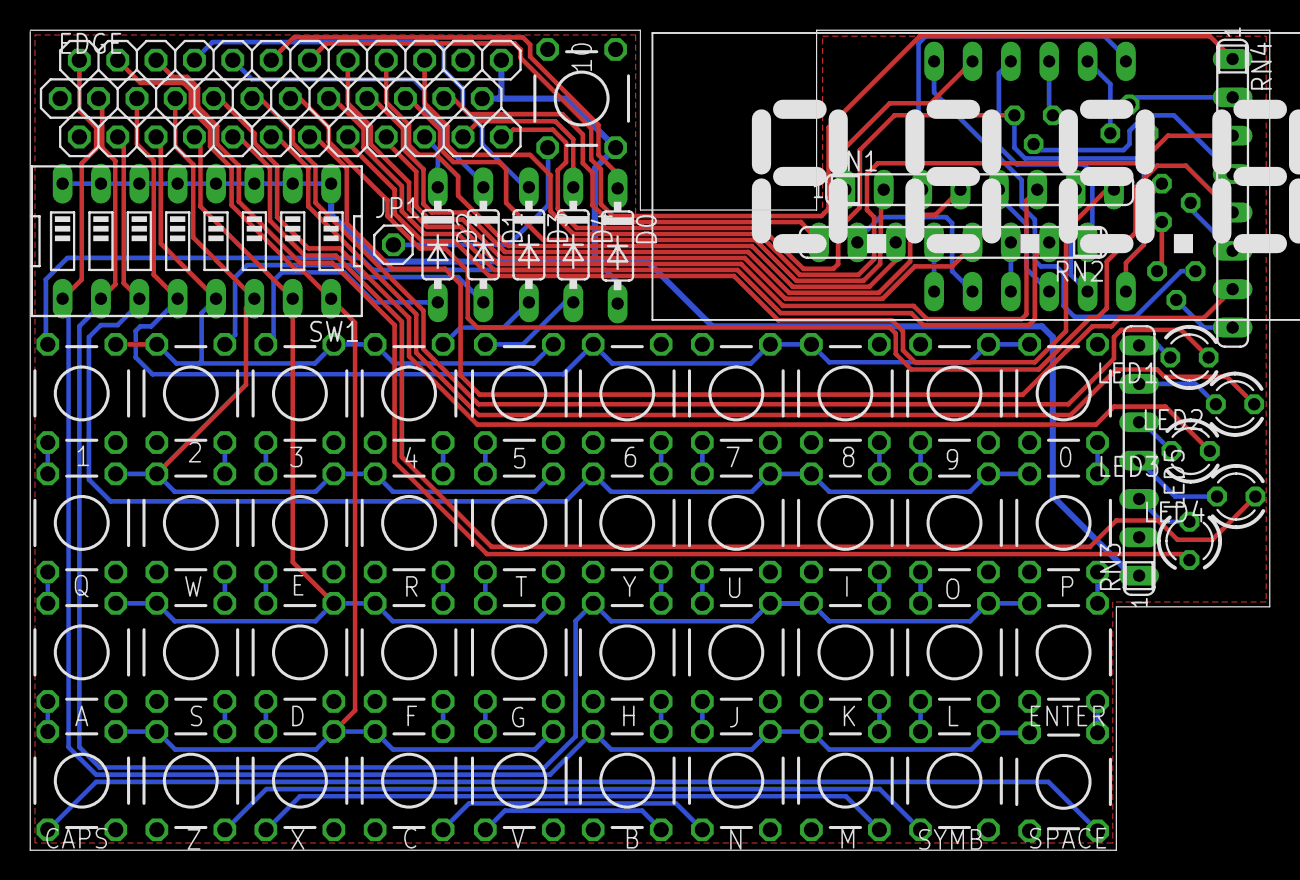
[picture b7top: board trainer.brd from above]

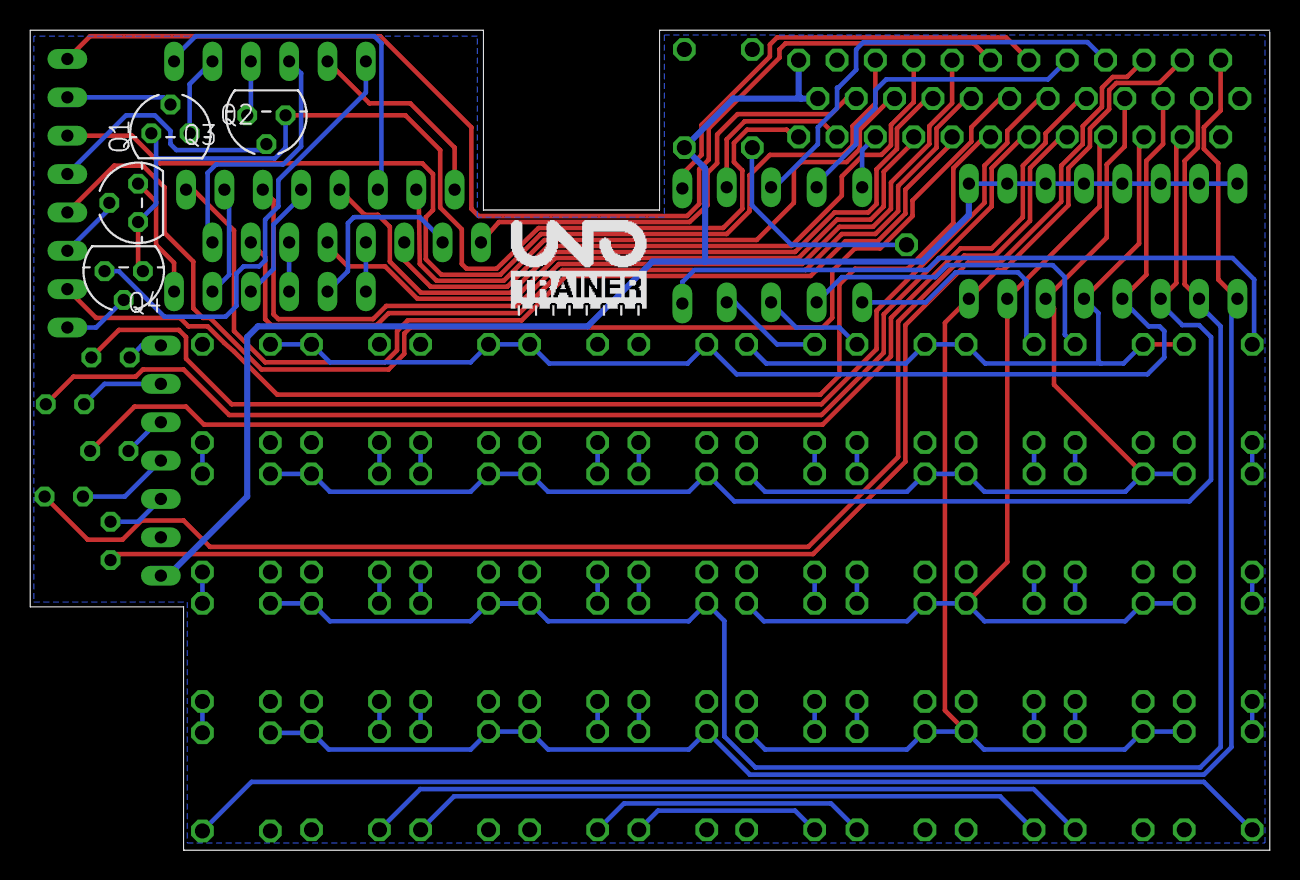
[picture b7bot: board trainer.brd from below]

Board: 2 copper layers, 82.1 x 54.3 mm, 63 parts (4 on the bottom side), 94 nets.

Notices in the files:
parts and their libraries:
SparkFun-Connectors: Licensing: CC v3.0 Share-Alike You are welcome to use this library for commercial purposes.
wuerth-elektronik: Copyright: Würth Elektronik eiSos
